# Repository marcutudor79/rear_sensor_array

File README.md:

# RSA = Rear Sensor Array

## Description
This code runs bare metal on Raspi Pi Pico.
<p>It collects data via I2C from an accelerometer / magnetometer</p>
<p>It also measures 2 suspension sensors</p>
<p>Parses data and sends it via CAN BUS</p>

<p>This is the accelerometer / magnetometer module which will be on the bottom part of the pcb</p>

<p>This is the can trasciever which will be on the upper part on the PCB, on the backside, in order to save some space</p>

<p>This is the RJ-45 THD connector which will on the most upper side of the PCB, you can see the holes in which it will reside</p>
<p>I also finished the design of the PCB for this module</p>
<p>It connects via an ethernet connector RJ-45 to the VCC GND and CAN bus of the car</p>
<p>This was a great choice, because the ethernet cables have a small footprint and 8 cables are already bundled toghether</p>

<p><i>Please beware of the jokes on the PCB Soldermask. They are greatly appreciated at Formula Student Comptetitions</i></p>

## This module is made for the FSA car of UPB Drive
Find us <a href="https://www.upbdrive.com/">here</a>

## File structure, explained
Here you wil find all the docs, pcb files and firware needed for RSA

## Other?
Nada

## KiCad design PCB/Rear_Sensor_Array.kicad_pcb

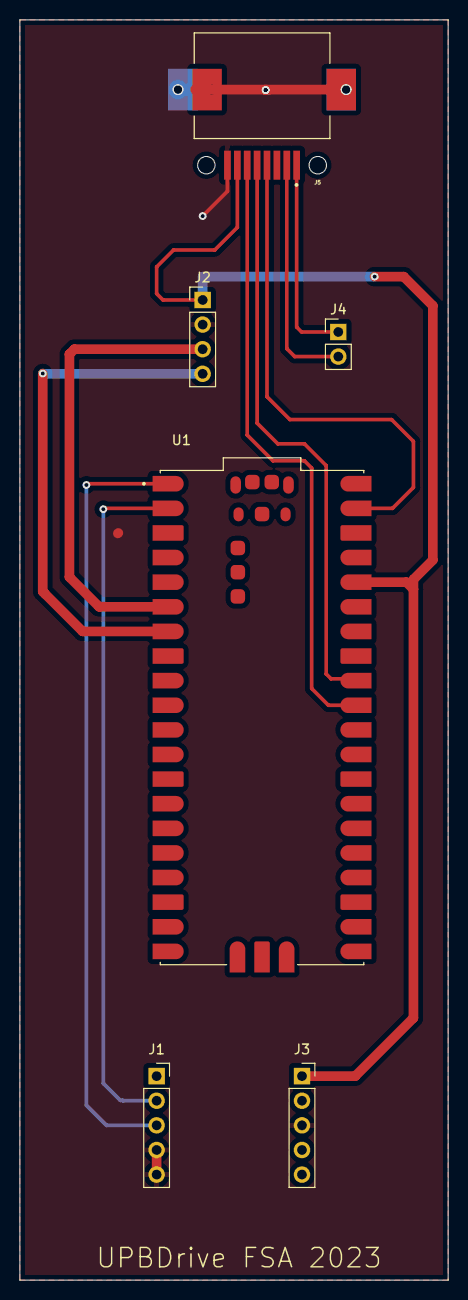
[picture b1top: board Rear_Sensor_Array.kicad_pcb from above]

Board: 2 copper layers, 44.2 x 130.0 mm, 6 parts (0 on the bottom side), 11 nets.

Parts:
J1, J3: Conn_01x05_Male; PinSocket_1x05_P2.54mm_Vertical
J2: Conn_01x04_Female; PinHeader_1x04_P2.54mm_Vertical
J4: Conn_01x02_Male; PinHeader_1x02_P2.54mm_Vertical
J5: 2041126-1; TE_2041126-1
U1: SC0915; MODULE_SC0915

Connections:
3.3V: J2.1, J3.1, J5.7, U1.36 (3V3_OUT)
5V: J5.4, U1.39 (VSYS)
CAN_H: J4.1, J5.1
CAN_L: J4.2, J5.2
CAN_RX: J2.3, U1.6 (GP4)
CAN_TX: J2.4, U1.7 (GP5)
GND: J1.4, J1.5, J2.2, J3.3, J5.8, J5.S1 (S), J5.S2 (S), U1.3 (GND), U1.8 (GND), U1.13 (GND), U1.18 (GND), U1.23 (GND), U1.28 (GND), U1.33 (AGND), U1.38 (GND), U1.D2 (GND)
POT_L: J5.5, U1.32 (GP27)
POT_R: J5.6, U1.31 (GP26)
SCL: J1.2, U1.2 (GP1)
SDA: J1.3, U1.1 (GP0)

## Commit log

2022-12-17 changes to readme
2023-02-28 update_v1_added_can_PIO
2023-02-28 update_firmware.cpp
2023-03-10 massive_update
2023-03-13 added_pcb_img
2023-03-13 Add CAN tranmission modularity
    #### Summary of changes
    * Refactor 1 line ifs. Even thought syntax allows it
    it's easier to read if these structures have braces
    around them as well.
    * Refactor error code. Usually 0 means succes.
    Tipically a -errno value is returnet to indicate the error.
